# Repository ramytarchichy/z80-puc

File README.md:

# Z80 PUC

Z80 PUC is a single-board Z80-based computer for embedded applications.

It's designed with all through-hole components for easy soldering and hacking,
as well as increased retro-cool factor. Despite its retro feel, all of its parts
are still readily available and in production as of writing this.

The goal is to have a Z80 "module" that can be quickly modified and then added
to a project instead of having to design and order a custom PCB every time.
Kind of like using a Raspberry Pi instead of designing your own ARM-based
computer for every project.

The "PUC" in Z80 **PUC** stands for "**P**revious **U**nit of **C**omputing".
Since the x86 CPUs in the Intel **NUC** (**N**ext **U**nit of **C**omputing) and
the Z80 both have a common ancestor (the Intel 8080 CPU), and both the NUC and
the Z80 PUC are small form factor computers, I thought it would be funny to call
them something similar.

# Memory map

## Memory

| From    | To      | Size | Use             |
|---------|---------|------|-----------------|
| `$0000` | `$1FFF` | 8K   | ROM             |
| `$2000` | `$3FFF` | 8K   | Banked Area RAM |
| `$4000` | `$7FFF` | 16K  | Bus Expansion   |
| `$8000` | `$FFFF` | 32K  | Static Area RAM |

## RAM Banks

The first 4 bits of Port B on the PIO select one out of 16 banks of 8K. The
static RAM area (`$8000`-`$FFFF`) is made up of 4 8K banks (`$C`-`$F`).

The total amount of addressable RAM built-in is 16x8K = 128K

## I/O

- The CTC uses I/O addresses `$00`-`$0F`.
- The PIO uses I/O addresses `$10`-`$1F`.

# Design choices

## Why a PIO instead of an SIO for interfacing with peripherals?

- The PIO gives us an additional 8 GPIO pins to play around with, 4 of which are
used for memory bank selection, and 1 for the on-board LED. Implementing those
without a PIO would increase component count, so since we're including it
regardless, might as well use it.
- Transferring 8 bits at a time is probably faster than serial, and if pin count
really is at a premium on your peripheral's microcontroller, you can still send
fewer bits at a time.
- The parallel interface works regardless of the peripheral's clock speed.
- It's what I already had lying around in the parts bin.

## Where are the CTC TRG and output pins?

I just included the CTC for timer interrupts. I've never needed any of the CTC's
other functionality, so I decided to save some space and not include a pin
header for that. If you really need it, you can just solder a few wires directly
to the board, or add an external CTC chip.

## Part Interchangeability

- 74HC137 <=> 74HC138
- AS6C1008 <=> AS6C4008
- AT28C64 <=> AT28C256

# License

Z80 PUC (c) by Ramy Tarchichy

Z80 PUC is licensed under a
Creative Commons Attribution-ShareAlike 4.0 International License.

You should have received a copy of the license along with this
work. If not, see [http://creativecommons.org/licenses/by-sa/4.0/](http://creativecommons.org/licenses/by-sa/4.0/).

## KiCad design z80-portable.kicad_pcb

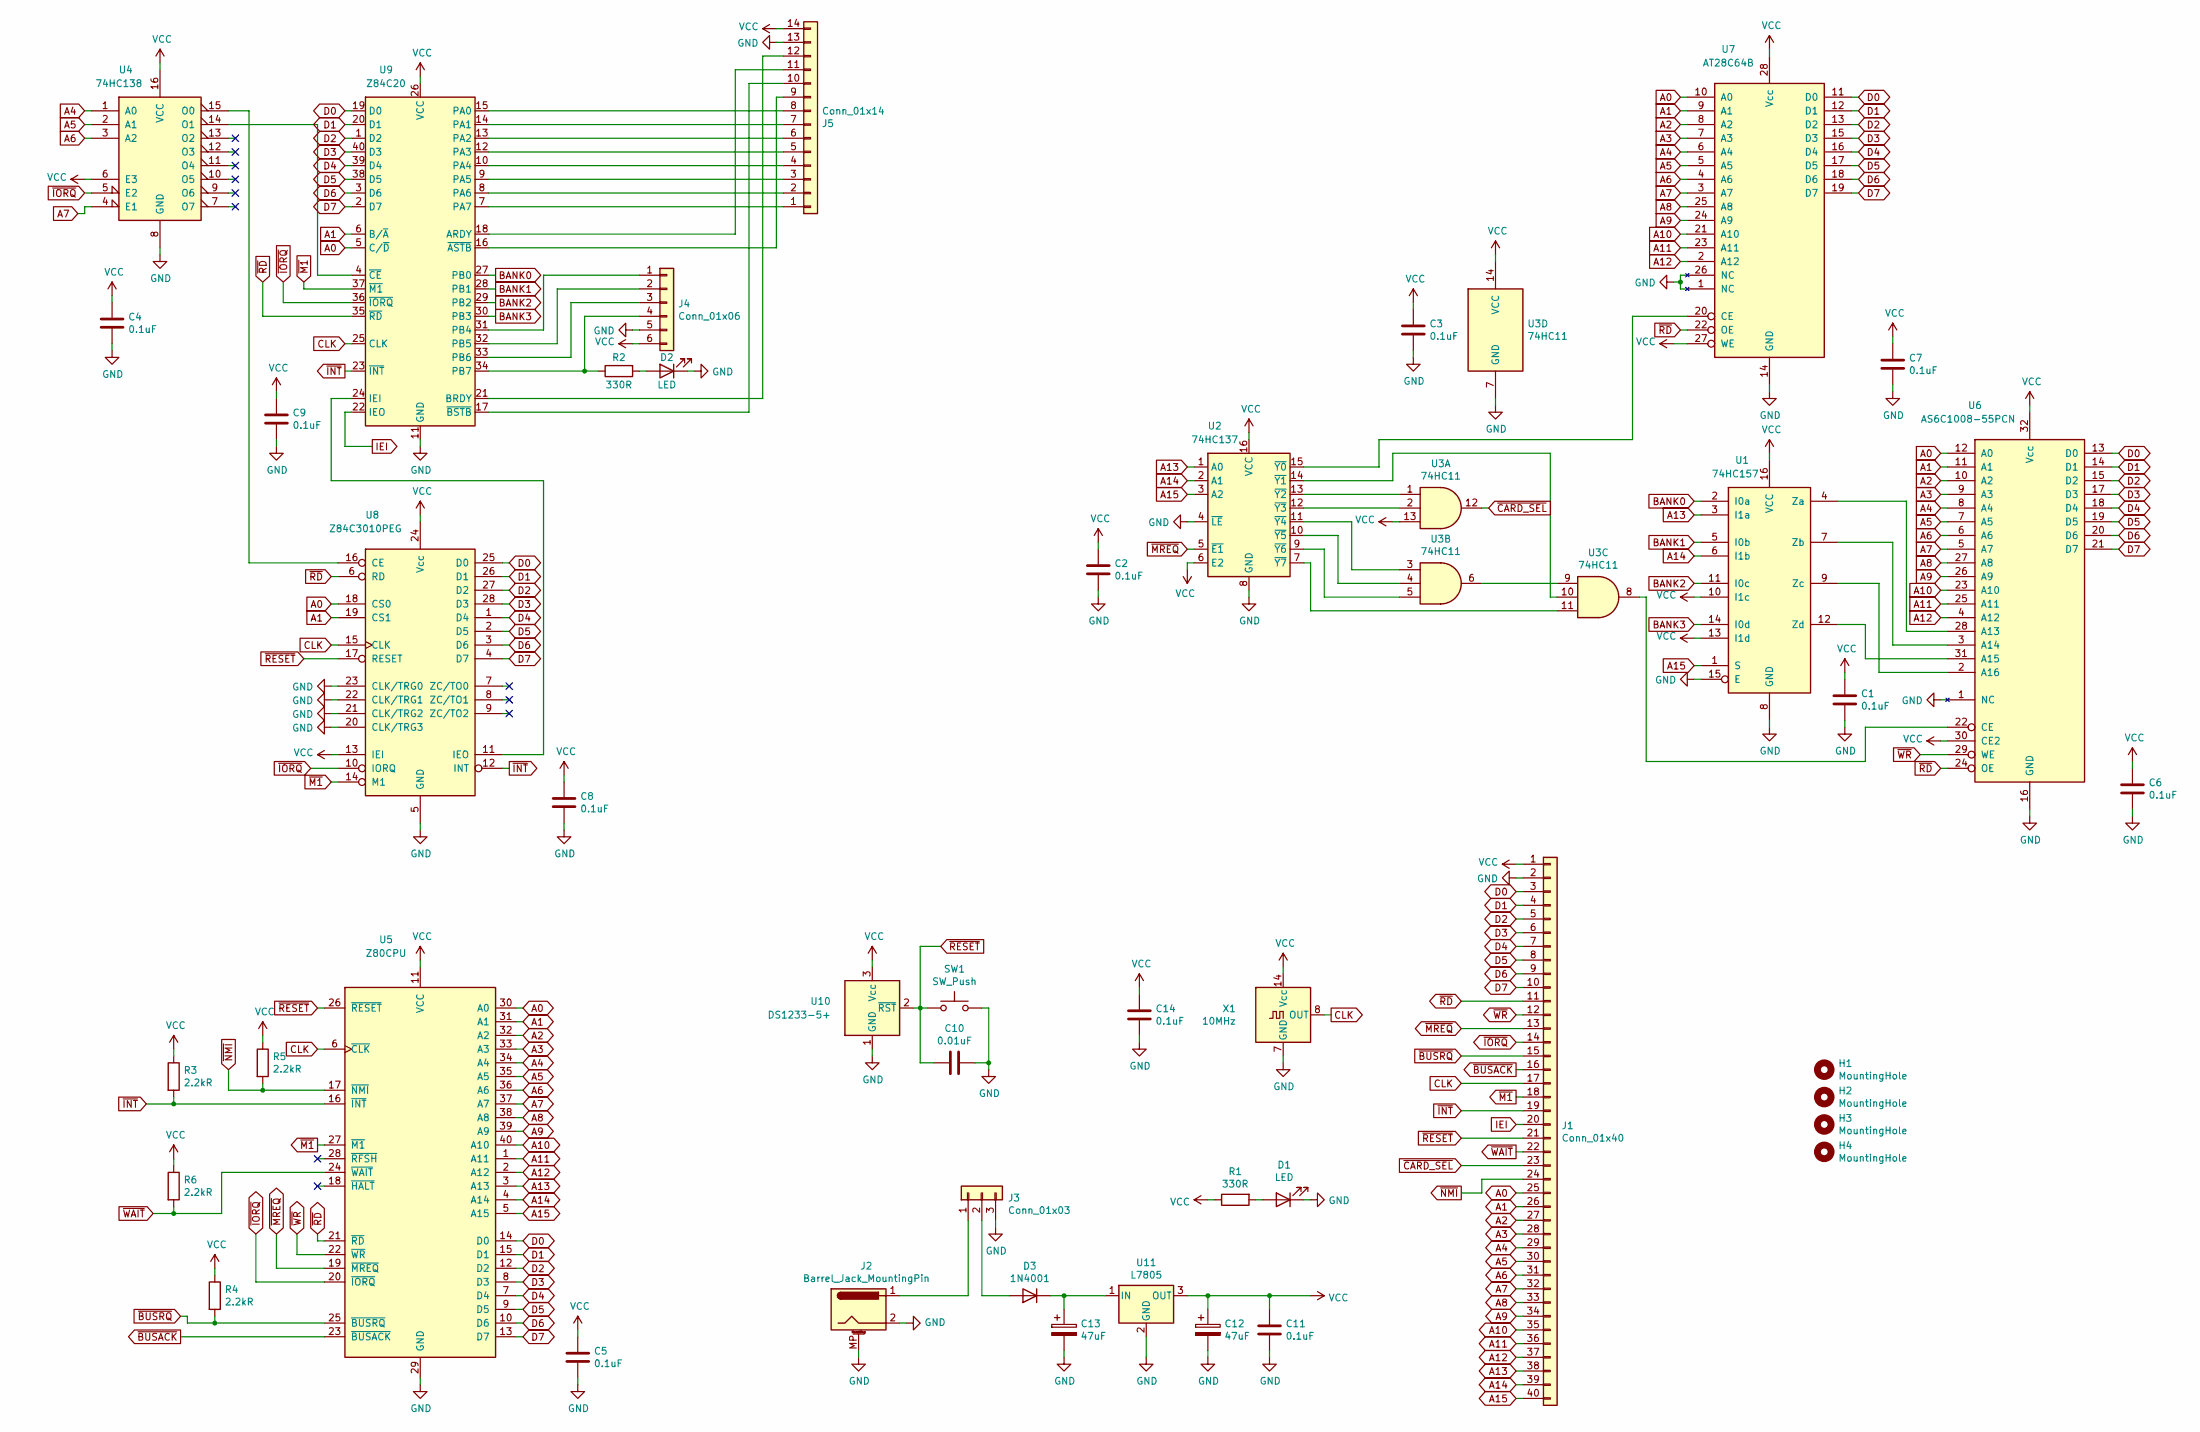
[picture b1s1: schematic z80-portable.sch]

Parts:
C1, C2, C3, C4, C5, C6, C7, C8, C9, C11, C14: 0.1uF; C_Disc_D5.0mm_W2.5mm_P2.50mm
C10: 0.01uF; C_Disc_D5.0mm_W2.5mm_P2.50mm
C12, C13: 47uF; CP_Radial_D5.0mm_P2.50mm
D1, D2: LED; LED_D5.0mm
D3: 1N4001; D_DO-41_SOD81_P7.62mm_Horizontal
H1, H2, H3, H4: MountingHole; MountingHole_3.2mm_M3
J1: Conn_01x40; PinSocket_2x20_P2.54mm_Horizontal
J2: Barrel_Jack_MountingPin; BarrelJack_Horizontal
J3: Conn_01x03; PinHeader_1x03_P2.54mm_Vertical
J4: Conn_01x06; PinHeader_2x03_P2.54mm_Vertical
J5: Conn_01x14; PinSocket_1x14_P2.54mm_Vertical
R1, R2: 330R; R_Axial_DIN0204_L3.6mm_D1.6mm_P5.08mm_Horizontal
R3, R4, R5, R6: 2.2kR; R_Axial_DIN0204_L3.6mm_D1.6mm_P5.08mm_Horizontal
SW1: SW_Push; SW_PUSH_6mm
U1: 74HC157; DIP-16_W7.62mm
U2: 74HC137; DIP-16_W7.62mm
U3: 74HC11; DIP-14_W7.62mm
U4: 74HC138; DIP-16_W7.62mm
U5: Z80CPU; DIP-40_W15.24mm
U6: AS6C1008-55PCN; DIP-32_W15.24mm
U7: AT28C64B; DIP-28_W15.24mm_Socket
U8: Z84C3010PEG; DIP-28_W15.24mm
U9: Z84C20; DIP-40_W15.24mm
U10: DS1233-5+; TO-92
U11: L7805; TO-220-3_Horizontal_TabDown
X1: 10MHz; Oscillator_DIP-14

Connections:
A0: J1.25, U5.30 (A0), U6.12 (A0), U7.10 (A0), U8.18 (CS0), U9.5 (C/~D~)
A1: J1.26, U5.31 (A1), U6.11 (A1), U7.9 (A1), U8.19 (CS1), U9.6 (B/~A~)
A2: J1.27, U5.32 (A2), U6.10 (A2), U7.8 (A2)
A3: J1.28, U5.33 (A3), U6.9 (A3), U7.7 (A3)
A4: J1.29, U4.1 (A0), U5.34 (A4), U6.8 (A4), U7.6 (A4)
A5: J1.30, U4.2 (A1), U5.35 (A5), U6.7 (A5), U7.5 (A5)
A6: J1.31, U4.3 (A2), U5.36 (A6), U6.6 (A6), U7.4 (A6)
A7: J1.32, U4.4 (E1), U5.37 (A7), U6.5 (A7), U7.3 (A7)
A8: J1.33, U5.38 (A8), U6.27 (A8), U7.25 (A8)
A9: J1.34, U5.39 (A9), U6.26 (A9), U7.24 (A9)
A10: J1.35, U5.40 (A10), U6.23 (A10), U7.21 (A10)
A11: J1.36, U5.1 (A11), U6.25 (A11), U7.23 (A11)
A12: J1.37, U5.2 (A12), U6.4 (A12), U7.2 (A12)
A13: J1.38, U1.3 (I1a), U2.1 (A0), U5.3 (A13)
A14: J1.39, U1.6 (I1b), U2.2 (A1), U5.4 (A14)
A15: J1.40, U1.1 (S), U2.3 (A2), U5.5 (A15)
BANK0: U1.2 (I0a), U9.27 (PB0)
BANK1: U1.5 (I0b), U9.28 (PB1)
BANK2: U1.11 (I0c), U9.29 (PB2)
BANK3: U1.14 (I0d), U9.30 (PB3)
CLK: J1.17, U5.6 (~CLK~), U8.15 (CLK), U9.25 (CLK), X1.8 (OUT)
D0: J1.3, U5.14 (D0), U6.13 (D0), U7.11 (D0), U8.25 (D0), U9.19 (D0)
D1: J1.4, U5.15 (D1), U6.14 (D1), U7.12 (D1), U8.26 (D1), U9.20 (D1)
D2: J1.5, U5.12 (D2), U6.15 (D2), U7.13 (D2), U8.27 (D2), U9.1 (D2)
D3: J1.6, U5.8 (D3), U6.17 (D3), U7.15 (D3), U8.28 (D3), U9.40 (D3)
D4: J1.7, U5.7 (D4), U6.18 (D4), U7.16 (D4), U8.1 (D4), U9.39 (D4)
D5: J1.8, U5.9 (D5), U6.19 (D5), U7.17 (D5), U8.2 (D5), U9.38 (D5)
D6: J1.9, U5.10 (D6), U6.20 (D6), U7.18 (D6), U8.3 (D6), U9.3 (D6)
D7: J1.10, U5.13 (D7), U6.21 (D7), U7.19 (D7), U8.4 (D7), U9.2 (D7)
GND: C1.2, C2.2, C3.2, C4.2, C5.2, C6.2, C7.2, C8.2, C9.2, C10.1, C11.2, C12.2, C13.2, C14.2, D1.1 (K), D2.1 (K), J1.2, J2.2, J2.MP (MountPin), J3.3, J4.5, J5.13, SW1.2, U1.8 (GND), U1.15 (E), U2.4 (~LE), U2.8 (GND), U3.7 (GND), U4.8 (GND), U5.29 (GND), U6.1 (NC), U6.16 (GND), U7.1 (NC), U7.14 (GND), U7.26 (NC), U8.5 (GND), U8.20 (CLK/TRG3), U8.21 (CLK/TRG2), U8.22 (CLK/TRG1), U8.23 (CLK/TRG0), U9.11 (GND), U10.1 (GND), U11.2 (GND), X1.7 (GND)
IEI: J1.20, U9.22 (IEO)
unnamed: C13.1, D3.1 (K), U11.1 (IN)
unnamed: D1.2 (A), R1.2
unnamed: D2.2 (A), R2.2
unnamed: D3.2 (A), J3.2
unnamed: J2.1, J3.1
unnamed: J4.1, U9.31 (PB4)
unnamed: J4.2, U9.32 (PB5)
unnamed: J4.3, U9.33 (PB6)
unnamed: J4.4, R2.1, U9.34 (PB7)
unnamed: J5.1, U9.7 (PA7)
unnamed: J5.2, U9.8 (PA6)
unnamed: J5.3, U9.9 (PA5)
unnamed: J5.4, U9.10 (PA4)
unnamed: J5.5, U9.12 (PA3)
unnamed: J5.6, U9.13 (PA2)
unnamed: J5.7, U9.14 (PA1)
unnamed: J5.8, U9.15 (PA0)
unnamed: J5.9, U9.16 (~ASTB~)
unnamed: J5.10, U9.17 (~BSTB~)
unnamed: J5.11, U9.18 (ARDY)
unnamed: J5.12, U9.21 (BRDY)
unnamed: U1.4 (Za), U6.28 (A13)
unnamed: U1.7 (Zb), U6.3 (A14)
unnamed: U1.9 (Zc), U6.2 (A16)
unnamed: U1.12 (Zd), U6.31 (A15)
unnamed: U2.7 (~Y7), U3.11
unnamed: U2.9 (~Y6), U3.5
unnamed: U2.10 (~Y5), U3.4
unnamed: U2.11 (~Y4), U3.3
unnamed: U2.12 (~Y3), U3.2
unnamed: U2.13 (~Y2), U3.1
unnamed: U2.14 (~Y1), U3.10
unnamed: U2.15 (~Y0), U7.20 (CE)
unnamed: U3.6, U3.9
unnamed: U3.8, U6.22 (CE)
unnamed: U4.14 (O1), U9.4 (~CE~)
unnamed: U4.15 (O0), U8.16 (CE)
unnamed: U8.11 (IEO), U9.24 (IEI)
VCC: C1.1, C2.1, C3.1, C4.1, C5.1, C6.1, C7.1, C8.1, C9.1, C11.1, C12.1, C14.1, J1.1, J4.6, J5.14, R1.1, R3.1, R4.1, R5.1, R6.1, U1.10 (I1c), U1.13 (I1d), U1.16 (VCC), U2.6 (E2), U2.16 (VCC), U3.13, U3.14 (VCC), U4.6 (E3), U4.16 (VCC), U5.11 (VCC), U6.30 (CE2), U6.32 (Vcc), U7.27 (WE), U7.28 (Vcc), U8.13 (IEI), U8.24 (Vcc), U9.26 (VCC), U10.3 (Vcc), U11.3 (OUT), X1.14 (Vcc)
~BUSACK: J1.16, U5.23 (~BUSACK~)
~BUSRQ: J1.15, R4.2, U5.25 (~BUSRQ~)
~CARD_SEL: J1.23, U3.12
~INT: J1.19, R3.2, U5.16 (~INT~), U8.12 (INT), U9.23 (~INT~)
~IORQ: J1.14, U4.5 (E2), U5.20 (~IORQ~), U8.10 (IORQ), U9.36 (~IORQ~)
~M1: J1.18, U5.27 (~M1~), U8.14 (M1), U9.37 (~M1~)
~MREQ: J1.13, U2.5 (~E1), U5.19 (~MREQ~)
~NMI: J1.24, R5.2, U5.17 (~NMI~)
~RD: J1.11, U5.21 (~RD~), U6.24 (OE), U7.22 (OE), U8.6 (RD), U9.35 (~RD~)
~RESET: C10.2, J1.21, SW1.1, U5.26 (~RESET~), U8.17 (RESET), U10.2 (~RST)
~WAIT: J1.22, R6.2, U5.24 (~WAIT~)
~WR: J1.12, U5.22 (~WR~), U6.29 (WE)

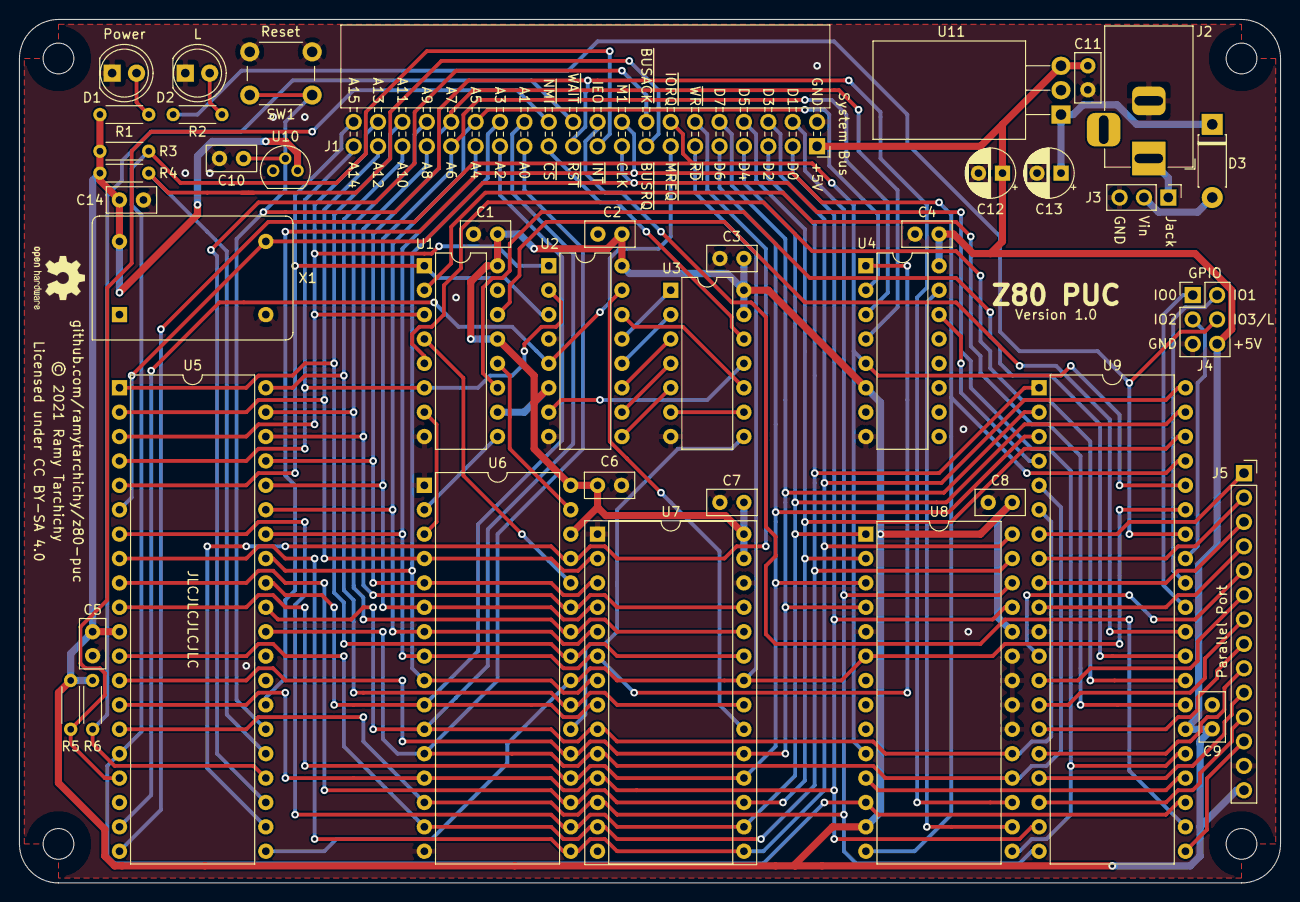
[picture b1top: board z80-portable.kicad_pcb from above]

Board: 2 copper layers, 131.3 x 89.9 mm, 45 parts (0 on the bottom side), 82 nets.

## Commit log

2021-12-04 Fixed a few minor mistakes, no need to reorder PCB

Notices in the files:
z80-portable.kicad_pcb:
© 2021 Ramy Tarchichy
Licensed under CC BY-SA 4.0
